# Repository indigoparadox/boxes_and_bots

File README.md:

# Boxes n' Bots

This is a monorepo containing various hardware projects and their firmwares, as well as less-common or WIP drivers for common components.

## Contents

### midimbox

Simple MIDI adaptor box designed to connect to PC gameport.

### sensehouse

Gather room sensor data using Adafruit Funhouse and push to MQTT.

### perfbox

Simple esp32-based prototype handheld gaming console.

### psuppet

A mobile metal box.

### thermterm

Modular mounted sensor box.

### sixlegs

Improvised/hacked convention freebie robot. 

### lcdbackpack

Tiny terminal based on the ESP32/SparkFun LCD Backpack.

### edsclock

Simple clock based on CircuitPython/QTPy and 2 displays and a HW clock from electricdollarstore.com.

### mqttcon

A console that displays incoming MQTT data.

### beepterm

Crammed a bunch of stuff into a 3D printed shell w/ esp8266.

### mspstat

A MSP430-based device that reads a DHT11 and displays the output on an LCD with a custom blinking anime girl face.

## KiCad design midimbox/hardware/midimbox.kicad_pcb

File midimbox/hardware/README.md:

# midimbox

Simple MIDI adaptor box designed to connect to PC gameport.

Notes:

- At present, output works, but input does not.
- TRS *or* DIN sockets may be used, but not both simultaneously.

Attributions:

- DIN-5 socket footprint taken from: http://smisioto.no-ip.org/elettronica/kicad/kicad-en.htm

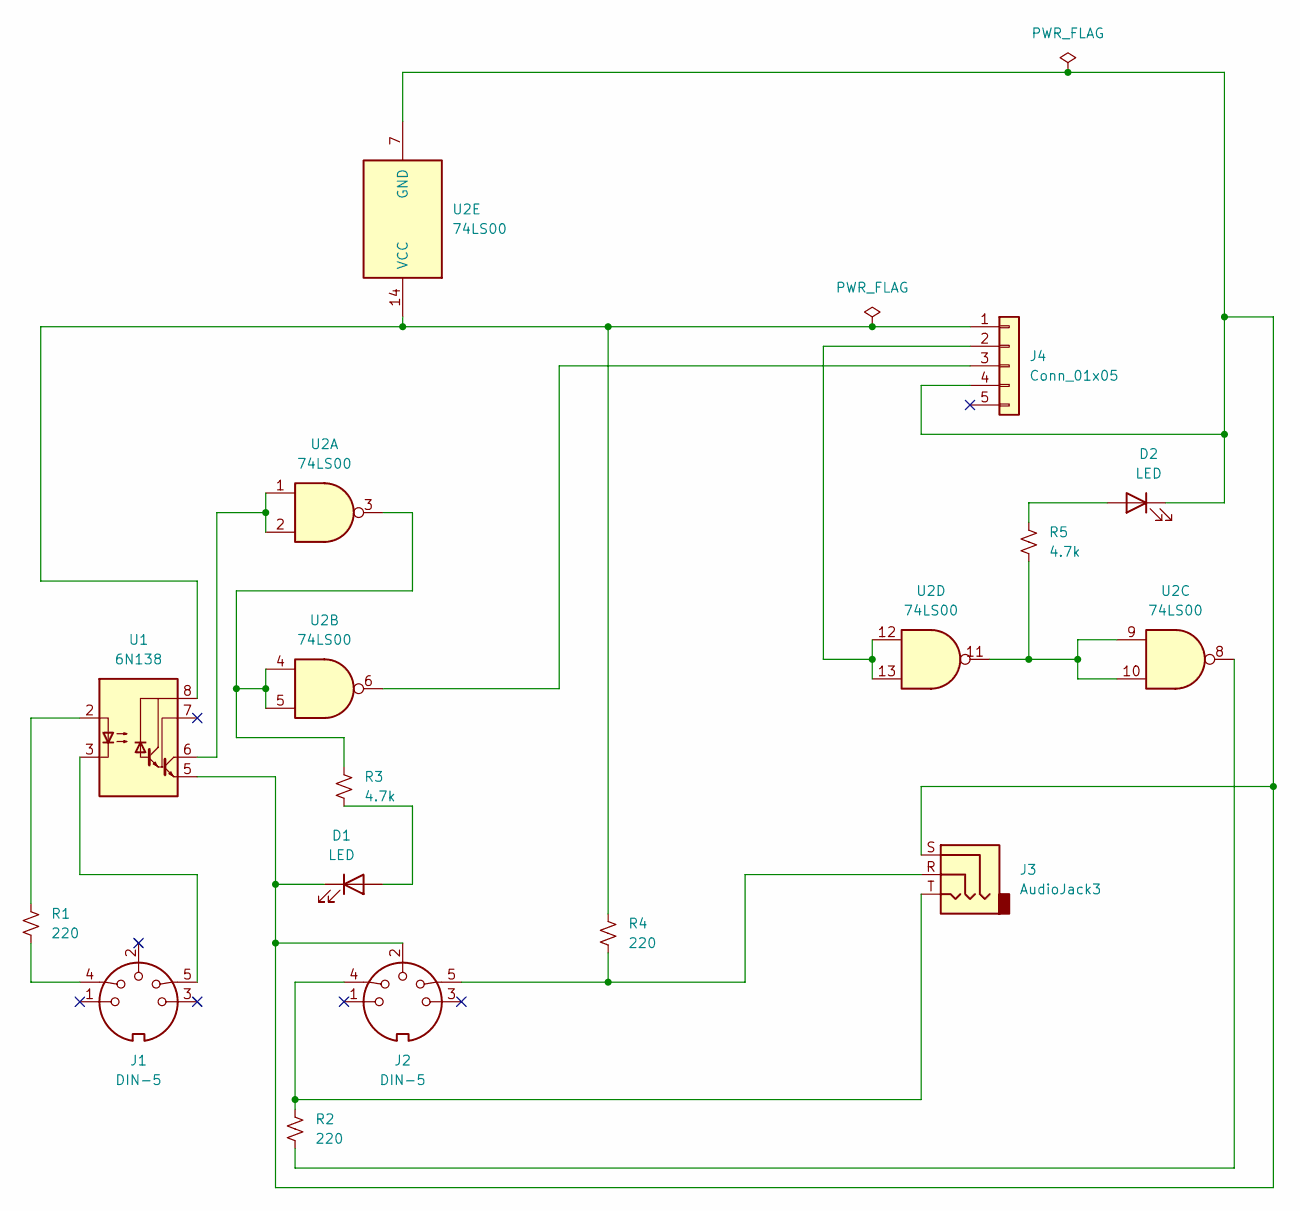
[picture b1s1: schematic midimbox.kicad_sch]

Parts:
D1, D2: LED; LED_D5.0mm
J1, J2: DIN-5; din-5
J3: AudioJack3; Jack_3.5mm_CUI_SJ1-3525N_Horizontal
J4: Conn_01x05; JST_EH_B5B-EH-A_1x05_P2.50mm_Vertical
R1, R2, R4: 220; R_Axial_DIN0204_L3.6mm_D1.6mm_P7.62mm_Horizontal
R3, R5: 4.7k; R_Axial_DIN0204_L3.6mm_D1.6mm_P7.62mm_Horizontal
U1: 6N138; DIP-8_W7.62mm_Socket
U2: 74LS00; DIP-14_W7.62mm_Socket

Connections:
unnamed: D1.1 (K), D2.1 (K), J2.2, J3.S, J4.4, U1.5 (GND), U2.7 (GND)
unnamed: D1.2 (A), R3.2
unnamed: D2.2 (A), R5.1
unnamed: J1.4, R1.2
unnamed: J1.5, U1.3 (C2)
unnamed: J2.4, J3.T, R2.1
unnamed: J2.5, J3.R, R4.2
unnamed: J4.1, R4.1, U1.8 (VCC), U2.14 (VCC)
unnamed: J4.2, U2.12, U2.13
unnamed: J4.3, U2.6
unnamed: R1.1, U1.2 (C1)
unnamed: R2.2, U2.8
unnamed: R3.1, U2.3, U2.4, U2.5
unnamed: R5.2, U2.9, U2.10, U2.11
unnamed: U1.6 (VO2), U2.1, U2.2

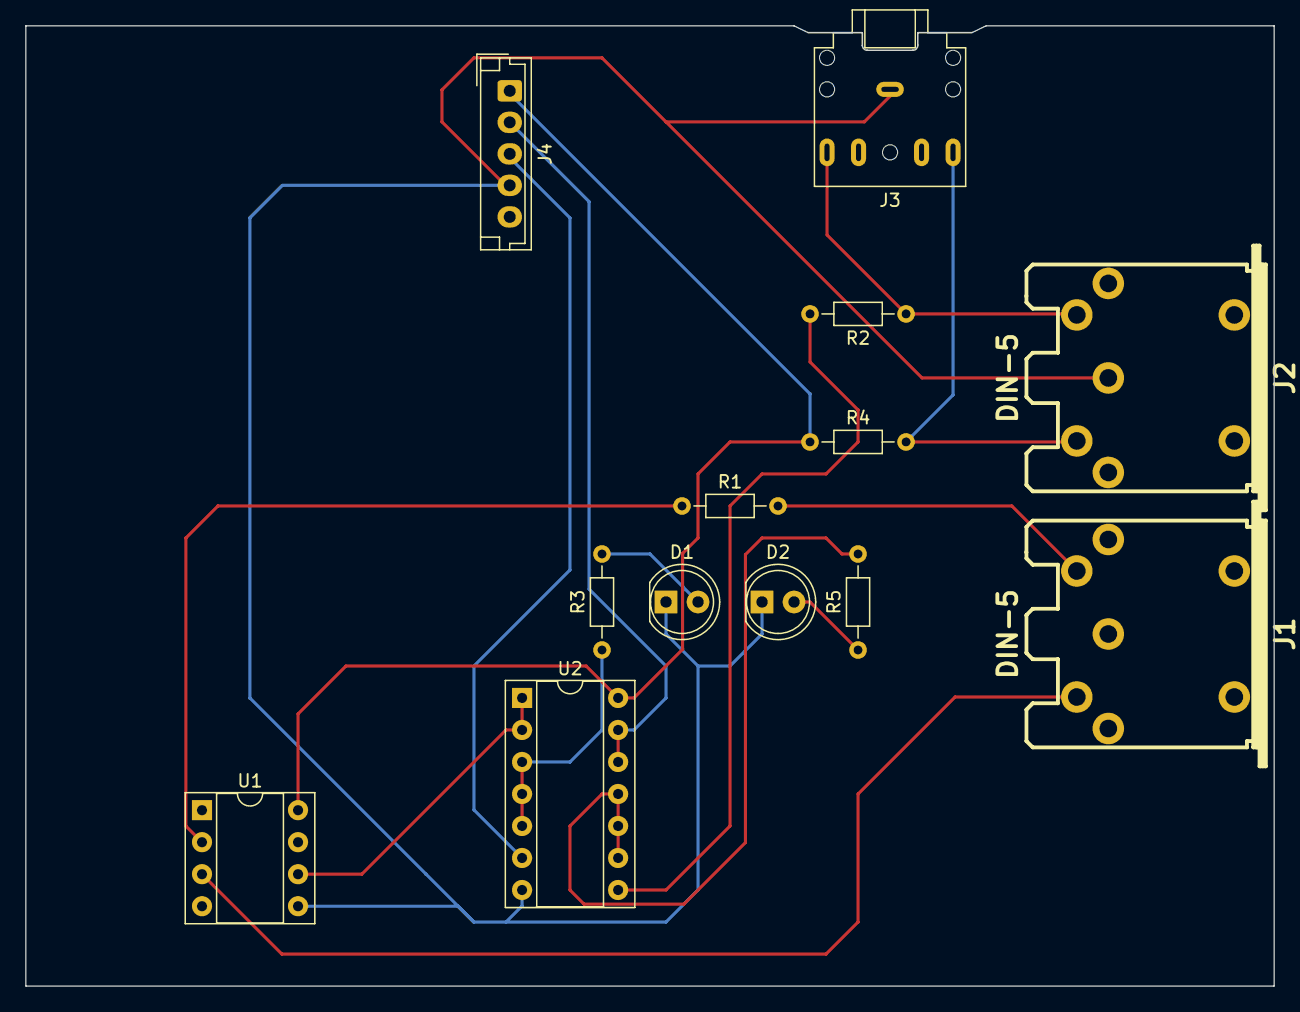
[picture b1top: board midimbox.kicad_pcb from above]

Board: 2 copper layers, 99.0 x 76.2 mm, 13 parts (0 on the bottom side), 15 nets.

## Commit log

2012-12-31 Initial revision.
2013-01-02 Supposedly we can establish a Bluetooth connection to the hardware now.
2013-01-02 Primary functions seem to work correctly.
2013-01-03 Tweaked the MAC UI to be a bit less of a hassle.
    TODO: Implement saving/restoring a non-default MAC.
2016-03-25 Have the UART talking, but we might be overthinking this.
2016-03-25 It now syncs after five tries.
2016-03-25 It now syncs pretty quickly after removing a silly typo.
2016-03-25 Broke command stuff into its own module. ESP8266 now resets and inits relatively cleanly.
2016-03-25 Tidying up and comments.
2016-03-28 Switched UART rx to use interrupts to better support network services.
2016-03-28 Implemented a super-rough server handler framework.
2016-03-28 Started to implement a sending routine.
2016-03-29 Removed a bunch of useless waiting and tidied things up a bit.
2016-03-29 Moved some more common stuff into boilerplate libraries.
2016-03-29 Pulled more stuff out of ISRs and into the main loop for handling requests.
2016-03-29 Fixed power management sleeping and cleaned up a bunch of warnings. Removed some unused stuff.
2016-03-29 Removed more delays in favor of sleeps.
2016-03-30 Attempting to add humidity sensor, but it's not talking yet (or sending is broken).
2019-06-07 shorten unnecessarily long filename
2019-06-07 refactor the methods and factor out crc function
2019-06-07 Rename methods and remove unused variable
2019-06-07 Remove unnecessary variables and fix whitespace
2019-06-07 Rewrite docs
2019-06-07 Remove unused ci/cd files
2019-06-07 Refactor unnecessary list unpacking
2019-06-22 Refactor unnecessary run command function
2020-11-08 Initial commit of testing minus drivers.
2020-11-08 Added module for cmucam5.
2020-11-08 Omit featureset check since it breaks with Adafruit breakout board.
2020-11-08 Added sgp30.
2020-11-08 Added GPL3.
2020-11-08 Ignore tempfiles and secrets.
2020-11-08 Rough MQTT/color/rotation control.
2020-11-08 Add robotcon and make MQTT more resilient. Start publishing.
2020-11-08 Bump cmucam5.
2020-11-09 Added umqttsimple2 and publishing metrics.
2020-11-09 Consolidate constants.
2020-11-10 Added walking and buzzer with some notices.
2020-11-13 Fixed some issues with buzz handling.
2020-11-19 Initial commit.
2020-11-19 Create LICENSE
2020-11-19 Incomplete initial version using HTTP.
2020-11-19 Switch to MQTT and stuff.
2020-11-22 Initial revision w/ polling for clicker.
2020-11-24 Make some unneeded pins optional.
2020-11-24 Added license.
2020-11-24 Revered ili9341 license.
2020-11-24 Added fill_rect.
2020-11-24 Added ssd1306 module.
2020-11-24 Moved ssd1306 to module.
2020-11-24 Added IRQ and sensor support and fleshed out UI.
2020-11-24 Added license and gitignore.
2021-03-19 Added BME680 support and improved display format.
2021-03-19 Pure python ili9341 and some experimental improvements.
2021-03-25 Added max1704.
2023-07-30 More modularity and display output.
2023-07-31 UI fixes.
2023-08-04 Use MQTT retain/last will.
2023-08-04 Added readme/license.
2023-08-04 README bump.
2023-08-10 More generalizing and polish.
2023-08-10 Added support dist files.
2023-08-10 Slightly more helpful README.
2023-08-11 Broke out polling into functions to support animation.
2023-08-12 Factored display into a class to hold state and not recreate groups.
2023-08-12 Added UI elements and rough button support.
2023-08-12 Switched to async model.
2023-08-12 Rough button support.
2025-02-17 Preparing to merge into boxes_and_bots.
2025-02-17 Be more specific.
2025-02-17 Remove gitmodules.
2025-02-17 Remove gitignore.
2025-02-17 Added blanket README.
2025-02-17 Organize drivers and update README.
2025-02-17 Link max1704 driver.
2025-02-17 Relinked max1704 and cmucam5.
2025-02-17 Relinked ssd1306.
2025-02-17 Relink ssd1306 and ili9341.
2025-02-17 Relink sgp30.
2025-02-17 Relink pca8574.
2025-02-19 Ported in skeleton of mqttcon.
2025-02-22 Moved beepterm into subdir.
2025-02-22 Added ssd1306 to beepterm.
2025-02-22 Added beepterm to README.
2025-02-22 Added psuppet icon.
2025-03-15 Prepare for boxes and bots merge.
2025-03-15 Removed .hgignore from mspstat.
2025-03-15 Added mspstat to README.
2025-04-01 extract encode+write+read+decode to _call() function
2025-04-01 add init(), get_version(), get_resolution(), set_brightness(), set_lamp(), get_rgb() functions
2026-05-29 fix coordinate splitting in get_rgb()
